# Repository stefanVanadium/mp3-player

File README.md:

# mp3-player

A modern hi-fi music player with a retro look. It plays FLAC/WAV through a proper DAC and headphone amp, streams to Bluetooth headphones, and has a reflective display you can read in direct sunlight.

<p align="center"><sub>41 × 101.9 × 8 mm, milled 6061 aluminium with a polished diamond-cut front edge, flush click wheel and cover glass, 3D printed antenna cap. Laser marked on the back.</sub></p>

## Enclosure

<p align="center"><sub>Rendered in Blender from the real model: the case parts from <code>enclosure/case.py</code> and the routed board exported from KiCad.</sub></p>

- **Body**: one tub milled from 6061, open at the back; front, sides and both ends in one piece
- **Back**: 0.7 mm aluminium plate on a 0.1 mm adhesive gasket, two M1.6 Torx screws; the top edge is held by the antenna cap
- **Antenna cap**: 3D printed, slides onto the top end like a pen cap (no metal over the ESP32 antenna)
- **Ports**: USB-C and the 3.5 mm jack sit in tight cutouts (0.1 mm around), about 0.2 mm under the bottom face
- **Checked against the board**: `enclosure/check.py` tests every case part against the real board STEP for collisions

## PCB

<p align="center"><sub>4-layer, 38.2 × 99.6 × 0.8 mm. Front: click wheel switches, display connector, DAC, headphone amp, USB-UART. Back: ESP32 module and microSD at the top, battery in the middle, charger, 3.3 V buck-boost and ± rails at the bottom.</sub></p>

## Highlights

- **Hi-fi audio path**: PCM5122 DAC (112dB, 32-bit/384kHz) → OPA1622 headphone amp powered from clean ± rails
- **FLAC / WAV / MP3** from a push-push microSD card
- **Bluetooth A2DP** to wireless headphones (classic ESP32)
- **3.5mm jack with plug detection**
- **Sunlight-readable display**: Sharp LS013B7DH03 memory LCD, crisp in direct sun and almost zero power
- **Soft power**: one button wakes the player from ship mode, and the ESP32 turns it off
- **USB-C**: charging, programming via USB-UART with auto-reset, and ESD protection
- **Real battery percentage** from a MAX17048 fuel gauge

## How it works

```
USB-C ─ ESD ─┬─ CP2102N ── ESP32-PICO-MINI-02
             └─ BQ25180 charger ── TPS63802 3.3V digital
                                ├─ LP5907 3.3V analog
                                └─ LM27762 ± rails
ESP32 ── I2S ── PCM5122 ── OPA1622 ── 3.5mm jack
      ├─ SDMMC ── microSD
      ├─ SPI ── display
      └─ BT ── headphones
```

Full architecture, BOM with JLCPCB stock/prices, who-solders-what, cost estimate and design notes are in **[mp3_player.md](mp3_player.md)**.

## Specs (planned)

| | |
|---|---|
| MCU | ESP32-PICO-MINI-02 (8MB flash, 2MB PSRAM) |
| DAC | PCM5122, hardware volume over I2C |
| Headphone amp | OPA1622 |
| Storage | microSD, 4-bit SDMMC |
| Display | Sharp LS013B7DH03 1.28" 128x128 memory LCD |
| Battery | LiPo pouch LP403759, 1000 mAh (4 mm thin) |
| Wireless | Bluetooth A2DP (SBC) |
| Board | 4-layer, 0.8 mm, assembled by JLCPCB + hand-soldered connectors |
| Case | CNC aluminium, anodized (titanium for v2), 41 × 101.9 × 8 mm |
| Prototype cost | ~$200 for 2 assembled boards (double-sided JLC assembly, checked 2026-11-19) |

## Repo layout

```
mp3_player.md         project documentation (start here)
mp3_player.kicad_*    KiCad 10 project
lib/                  symbols, footprints, 3D models (generated from LCSC parts)
datasheets/           datasheets for every chosen part
connections.md        pin-by-pin schematic connections and datasheet review
code.md               firmware notes (hardware limits, first boot)
firmware/             PlatformIO firmware: player + bring-up menu
enclosure/            case model (build123d): case.py, check.py, full.py, Blender render scripts
images/               PCB and product renders
mp3_player.tex/.pdf   printable writeup
```

## Status

- [x] Requirements, architecture, BOM
- [x] KiCad libraries + datasheets
- [x] Schematic (5 sheets: USB, power, ESP32, audio, I/O)
- [x] Case concept (parametric model, two variants)
- [x] Final case model (milled unibody, collision-checked against the board) + photoreal renders
- [x] PCB: placement, routing (4 layers, DRC clean), silkscreen
- [x] Fab files (Gerbers, drill, JLC BOM + CPL)
- [ ] Order (re-check stock first)
- [ ] Firmware: draft in `firmware/` (`arduino-audio-tools` + `ESP32-A2DP`), compiles, not yet run on hardware

## License

[MIT](LICENSE) for the design files and documentation in this repo. Datasheets in `datasheets/` belong to their manufacturers. Footprints and 3D models in `lib/` were generated from EasyEDA/LCSC data.

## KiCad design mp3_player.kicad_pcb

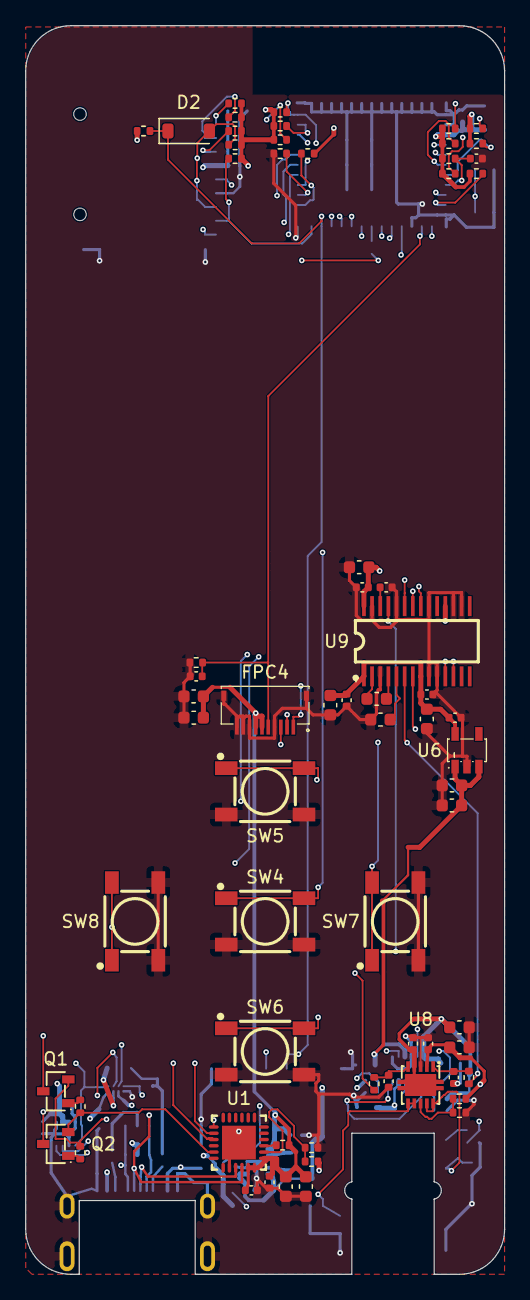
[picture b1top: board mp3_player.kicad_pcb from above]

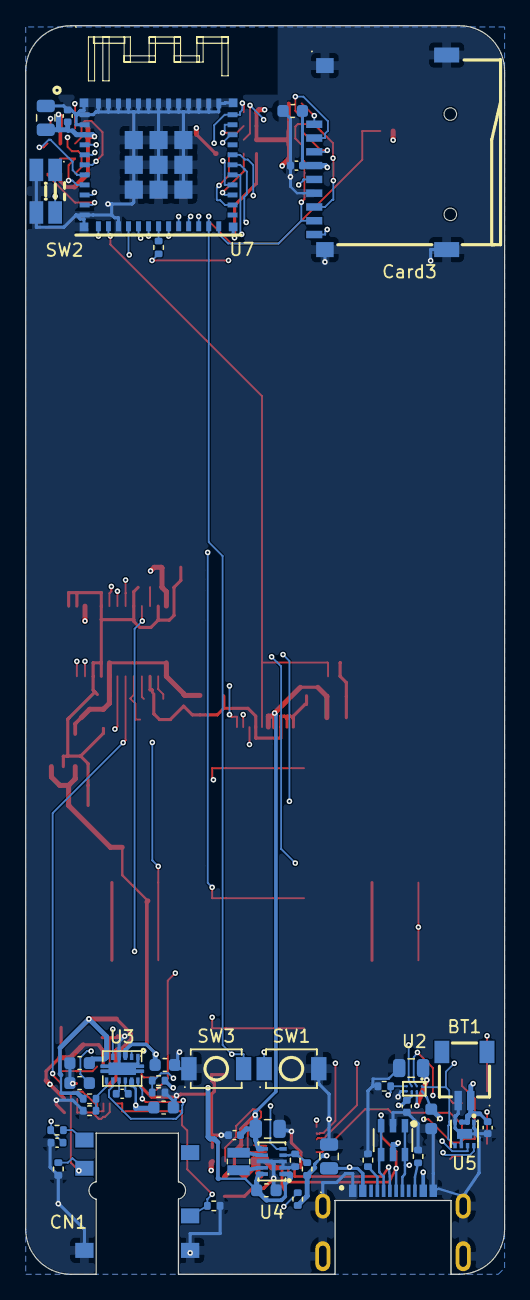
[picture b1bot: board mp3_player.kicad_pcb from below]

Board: 4 copper layers, 38.2 x 99.6 mm, 113 parts (46 on the bottom side), 69 nets.

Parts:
BT1: Battery_Cell; CONN-SMD_2P-P1.00_SM02B-SRSS-TB-LF-SN
C1, C3, C6, C7, C11, C16, C18, C20, C22, C24, C25, C26, C28, C30, C33, C35, C37, C40, C41: C; C_0402_1005Metric
C2, C5, C8, C10, C12, C13, C14, C15, C19, C21, C27, C29, C31, C32, C34, C36, C38, C39, C42, C43: C; C_0603_1608Metric
C4, C9, C17, C23: C; C_0805_2012Metric
C44: 100nF; C_0402_1005Metric
CN1: PJ-342C CB; AUDIO-SMD_HX-PJ-342C
Card3: TF-01A; TF-SMD_TF-01A
D1: USBLC6-2SC6; SOT-23-6_L2.9-W1.6-P0.95-LS2.8-BL
D2: D_Schottky; D_SOD-123
FPC4: FH19C-10S-0.5SH(10); FPC-SMD_10P-P0.50_FH19C-10S-0.5SH-10
L1: WPN201610HR47MT; IND-SMD_L2.0-W1.6_WPN2016X
Q1, Q2: MMBT3904-C20526; SOT-23-3_L2.9-W1.3-P1.90-LS2.4-BR
R1, R2, R3, R4, R5, R6, R7, R8, R9, R10, R11, R12, R13, R14, R15, R16, R17, R18, R19, R20, R21, R22, R23, R24, R25, R26, R27, R28, R29, R30, R31, R32, R33, R34, R35, R36, R37, R38, R39, R40, R41, R42: R; R_0402_1005Metric
SW1, SW3: TS-1088-AR02016; SW-SMD_L3.9-W3.0-P4.45
SW2: EVQP7J01P; SW-SMD_EVQP7J01P
SW4, SW5, SW6, SW7, SW8: TS-1187B-B; KEY-SMD_4P-L4.8-W4.8-P3.70-LS6.4-TL
U1: CP2102N-A02-GQFN24R; QFN-24_L4.0-W4.0-P0.50-TL-EP2.6
U2: BQ25180YBGR; DSBGA-8_L1.6-W0.9-R2-C4-P0.40-BL
U3: LM27762DSSR; WSON-12_L3.0-W2.0-P0.50-BL-EP
U4: TPS63802DLAR; VSON-10_L3.0-W2.0-P0.50-TL
U5: MAX17048G+T10; TDFN-8_L2.0-W2.0-P0.50-BL-EP1.2
U6: LP5907MFX-3.3/NOPB; SOT-23-5_L3.0-W1.7-P0.95-LS2.8-BR
U7: ESP32-PICO-MINI-02-N8R2; BULETM-SMD_ESP32-PICO-MINI-02-N8R2
U8: OPA1622IDRCR; VSON-10_L3.0-W3.0-P0.50-BL-EP1.65
U9: PCM5122PW; TSSOP-28_L9.8-W6.6-P0.65-BL
USB1: TYPE-C 16P CB0.8 073; USB-C-SMD_TYPE-C-16P-CB0.8-073

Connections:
+3V0_AMP: C8.2, C30.1, C31.1, R13.1, R39.1, U3.11 (OUT+), U8.2 (V+)
+3V3: C2.1, C3.1, C5.1, C6.1, C16.1, C17.1, C22.1, C23.1, C28.1, C29.1, C39.2, C40.2, C42.1, C43.1, Card3.4 (VDD), FPC4.6, FPC4.7, R3.1, R4.1, R7.1, R15.2, R17.2, R18.2, R19.2, R20.2, R21.2, R22.2, R24.2, R25.2, R26.2, R27.2, R28.2, R29.2, R30.2, R31.2, R32.2, R42.1, U1.5 (VIO), U1.6 (VDD), U1.7 (VREGIN), U4.6 (VOUT), U7.3 (3V3), U9.18 (MODE2), U9.28 (DVDD)
+3V3_A: C20.2, C26.1, C27.1, C35.1, C36.1, U6.5 (OUT), U9.1 (CPVDD), U9.8 (AVDD)
-3V0_AMP: C14.2, C37.1, C38.1, R14.2, U3.6 (OUT–), U8.4 (V-), U8.11 (V-(EP))
AMP_INL: C24.2, R35.1, U8.1 (+INA)
AMP_INR: C25.1, R36.2, U8.5 (+INB)
AUDIO_EN: R33.1, U3.8 (EN–), U3.12 (EN+), U7.27 (IO7), U9.25 (XSMT)
BTN_NEXT: R19.1, SW7.1, U7.5 (I37)
BTN_PLAY: R31.1, SW4.1, U7.26 (IO20)
BTN_PREV: R20.1, SW8.1, U7.6 (I38)
BTN_VOLDN: R22.1, SW6.1, U7.10 (I35)
BTN_VOLUP: R21.1, SW5.1, U7.9 (I34)
DAC_L: R35.2, U9.6 (OUTL)
DAC_R: R36.1, U9.7 (OUTR)
DTR: Q2.2 (E), R5.1, U1.23 (DTR)
ESP_BOOT: D2.1 (K), Q2.3 (C), R4.2, SW3.1, U7.23 (IO0)
ESP_EN: C1.2, Q1.3 (C), R3.2, SW1.2, U7.8 (EN)
ESP_RX: U1.21 (TXD), U7.30 (RXD0)
ESP_TX: U1.20 (RXD), U7.31 (TXD0)
GND: BT1.2 (-), C1.1, C2.2, C3.2, C4.2, C5.2, C6.2, C7.2, C8.1, C9.2, C10.2, C12.1, C13.2, C14.1, C15.1, C16.2, C17.2, C18.2, C19.2, C20.1, C21.1, C22.2, C23.2, C24.1, C25.2, C26.2, C27.2, C28.2, C29.2, C30.2, C31.2, C33.1, C34.1, C35.2, C36.2, C37.2, C38.2, C39.1, C40.1, C41.2, C42.2, C43.2, C44.1, CN1.1 (MIC), CN1.2 (GND), Card3.6 (VSS), Card3.10 (GND), Card3.11 (GND), Card3.12 (GND), Card3.13 (GND), D1.2, FPC4.4, FPC4.8, FPC4.9, FPC4.10, FPC4.11, FPC4.12, R1.2, R2.2, R9.1, R10.2, R11.2, R12.1, R16.2, R23.2, R33.2, R34.2, R37.2, R38.2, SW1.1, SW2.2, SW3.2, SW4.2, SW5.2, SW6.2, SW7.2, SW8.2, U1.2 (GND), U1.25 (GND), U2.D2 (GND), U3.1 (PGOOD), U3.4 (GND), U3.13 (EP), U4.2 (MODE), U4.3 (AGND), U4.8 (GND), U5.1 (CTG), U5.4 (GND), U5.6 (QSTRT), U5.9 (EP), U6.2 (GND), U7.1 (GND), U7.2 (GND), U7.11 (GND), U7.14 (GND), U7.36 (GND), U7.37 (GND), U7.38 (GND), U7.39 (GND), U7.40 (GND), U7.41 (GND), U7.42 (GND), U7.43 (GND), U7.44 (GND), U7.45 (GND), U7.46 (GND), U7.47 (GND), U7.48 (GND), U7.49 (GND), U7.50 (GND), U7.51 (GND), U7.52 (GND), U7.53 (GND), U8.3 (GND), U9.3 (CPGND), U9.9 (AGND), U9.10 (VCOM), U9.16 (ADR2), U9.17 (MODE1), U9.20 (SCK), U9.24 (ADR1), U9.27 (DGND), USB1.0, USB1.A1B12 (GND), USB1.B1A12 (GND)
HP_L: CN1.4 (AU-L), R37.1, U8.9 (OUTA), U8.10 (-INA)
HP_R: CN1.3 (AU-R), R34.1, U8.6 (-INB), U8.7 (OUTB)
I2C_SCL: R25.1, U2.B1 (SCL), U5.7 (SCL), U7.34 (IO22), U9.12 (SCL)
I2C_SDA: R24.1, U2.C1 (SDA), U5.8 (SDA), U7.35 (IO21), U9.11 (SDA)
I2S_BCK: U7.16 (IO26), U9.21 (BCK)
I2S_DOUT: U7.17 (IO27), U9.22 (DIN)
I2S_LRCK: U7.15 (IO25), U9.23 (LRCK)
JACK_DET: C44.2, R41.1, R42.2, U7.7 (I39)
JACK_SW: CN1.6 (HP-DET), R41.2
LCD_CS: FPC4.3, U7.12 (IO32)
LCD_DISP: C41.1, FPC4.5, R23.1, U7.13 (IO33)
LCD_MOSI: FPC4.2, U7.33 (IO19)
LCD_SCK: FPC4.1, U7.29 (IO5)
unnamed: Card3.5 (CLK(SCLK)), R40.1
unnamed: Q1.1 (B), R5.2
unnamed: Q2.1 (B), R6.2
unnamed: R7.2, U1.9 (RSTb)
unnamed: R8.2, R9.2, U1.8 (VBUS)
unnamed: R12.2, SW2.1, U2.D1 (TS/MR)
unnamed: C11.1, U3.10 (C1+)
unnamed: C11.2, U3.9 (C1–)
unnamed: C13.1, U3.5 (CP)
unnamed: R10.1, R13.2, U3.2 (FB+)
unnamed: R11.1, R14.1, U3.7 (FB–)
unnamed: R15.1, R16.1, U4.4 (FB)
unnamed: L1.1, U4.9 (L1)
unnamed: L1.2, U4.7 (L2)
unnamed: R17.1, U4.5 (PG)
unnamed: R38.1, R39.2, U8.8 (EN)
unnamed: C32.2, U9.4 (CAPM)
unnamed: C32.1, U9.2 (CAPP)
unnamed: C33.2, U9.26 (LDOO)
unnamed: C34.2, U9.5 (VNEG)
unnamed: R2.1, USB1.A5 (CC1)
unnamed: R1.1, USB1.B5 (CC2)
PWR_INT: R32.1, U2.A1 (/INT), U5.5 (~ALRT), U7.28 (IO8)
RTS: Q1.2 (E), R6.1, U1.19 (RTS)
SD_CLK: R40.2, U7.18 (IO14)
SD_CMD: Card3.3 (CMD(DI)), R28.1, U7.21 (IO15)
SD_D0: Card3.7 (DAT0(D0)), D2.2 (A), R29.1, U7.22 (IO2)
SD_D1: Card3.8 (DAT1(RSV)), R30.1, U7.24 (IO4)
SD_D2: Card3.1 (DAT2(RSV)), R26.1, U7.19 (IO12)
SD_D3: Card3.2 (CDDAT3(CS)), R27.1, U7.20 (IO13)
SD_DET: Card3.9 (CD), R18.1, U7.4 (I36)
USB_DN: D1.3, D1.4, U1.4 (D-), USB1.A7 (DN1), USB1.B7 (DN2)
USB_DP: D1.1, D1.6, U1.3 (D+), USB1.A6 (DP1), USB1.B6 (DP2)
VBAT: BT1.1 (+), C7.1, C18.1, U2.C2 (BAT), U5.2 (CELL), U5.3 (VDD)
VBUS: C4.1, C10.1, D1.5, R8.1, U2.A2 (IN), USB1.A4B9 (VBUS), USB1.B4A9 (VBUS)
VSYS: C9.1, C12.2, C15.2, C19.1, C21.2, U2.B2 (SYS), U3.3 (VIN), U4.1 (EN), U4.10 (VIN), U6.1 (IN), U6.3 (EN)

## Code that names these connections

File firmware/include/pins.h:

// ESP32-PICO-MINI-02 pin map. Source of truth: ../connections.md, section 3.
#pragma once

namespace pins {
// I2C: BQ25180 (0x6A), MAX17048 (0x36), PCM5122 (0x4C)
constexpr int I2C_SDA = 21;
constexpr int I2C_SCL = 22;

// I2S to the PCM5122 (no MCLK: the DAC's PLL runs from BCK)
constexpr int I2S_BCK = 26;
constexpr int I2S_LRCK = 25;
constexpr int I2S_DOUT = 27;

// microSD: SDMMC slot 1, 4-bit, fixed IO_MUX pins (CLK 14, CMD 15, D0 2, D1 4, D2 12, D3 13)

// Sharp LS013B7DH03 memory LCD
constexpr int LCD_SCK = 5;
constexpr int LCD_MOSI = 19;
constexpr int LCD_CS = 32;    // SCS, active HIGH
constexpr int LCD_DISP = 33;  // 100k pull-down: panel blank until initialized

// Click wheel, active LOW, external 10k pull-ups (34..38 are input-only)
constexpr int BTN_PLAY = 20;
constexpr int BTN_VOLUP = 34;
constexpr int BTN_VOLDN = 35;
constexpr int BTN_NEXT = 37;
constexpr int BTN_PREV = 38;

// Audio power: HIGH enables LM27762 (+-rails for the OPA1622) and releases PCM5122 XSMT
constexpr int AUDIO_EN = 7;

// BQ25180 /INT (128 us pulse) wired-OR with MAX17048 ALRT, 10k pull-up
constexpr int PWR_INT = 8;

// Detect lines on GPIO36/39: poll with debounce (ESP32 errata), never as interrupts
constexpr int SD_DET = 36;    // LOW = card inserted (to verify on the first board)
constexpr int JACK_DET = 39;  // LOW = headphones plugged in

// GPIO0 is boot-only (diode to SD D0). Never drive it at runtime.
}  // namespace pins
